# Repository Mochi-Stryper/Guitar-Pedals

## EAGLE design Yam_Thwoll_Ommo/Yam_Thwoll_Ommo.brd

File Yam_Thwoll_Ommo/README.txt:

Zvex
Woolly Mammoth
Wool (Fuzz/Gain) - B2k
Pinch (Gate) - B500k
EQ - B10k
Volume - B10k

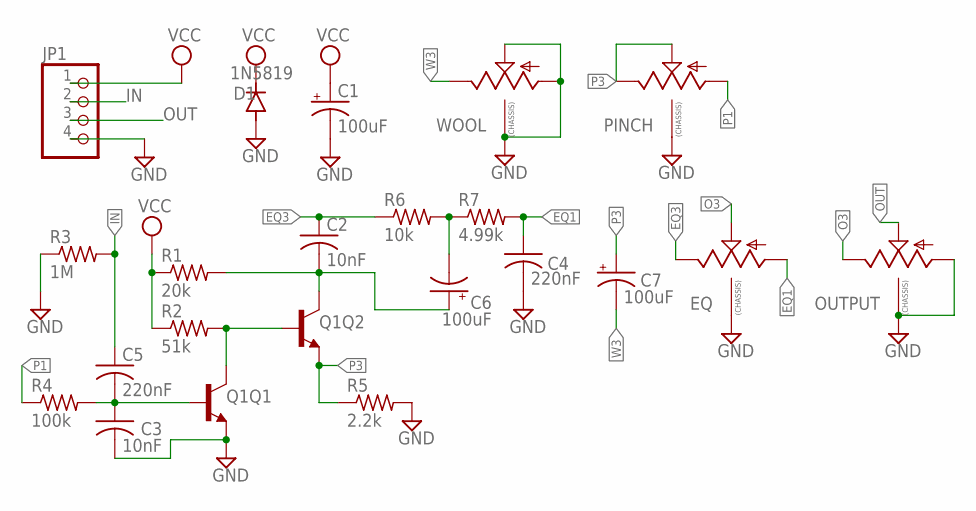
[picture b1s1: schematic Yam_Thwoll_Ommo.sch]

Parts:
C1, C6, C7: 100uF; PAN_B_SMD+THRU
C2, C3: 10nF; C0402
C4, C5: 220nF; C0402
D1: 1N5819; SOD123
EQ: 9MM_SNAP-IN_POT_CHASSIS; 9MM_SNAP-IN_POT
JP1: PINHD-1X4; 1X04
OUTPUT: 9MM_SNAP-IN_POT_CHASSIS; 9MM_SNAP-IN_POT
PINCH: 9MM_SNAP-IN_POT_CHASSIS; 9MM_SNAP-IN_POT
Q1: TRANS_NPN_DUAL-MBT3904DW1T1; SC70-6
R1: 20k; R0402
R2: 51k; R0402
R3: 1M; R0402
R4: 100k; R0402
R5: 2.2k; R0402
R6: 10k; R0402
R7: 4.99k; R0402
WOOL: 9MM_SNAP-IN_POT_CHASSIS; 9MM_SNAP-IN_POT

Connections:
EQ1: C4.1, EQ.1 (A), R7.2
EQ3: C2.1, EQ.3 (E), R6.1
GND: C1.-, C1.-- (-), C3.2, C4.2, D1.A, EQ.CHASSIS1, EQ.CHASSIS2, JP1.4, OUTPUT.1 (A), OUTPUT.CHASSIS1, OUTPUT.CHASSIS2, PINCH.CHASSIS1, PINCH.CHASSIS2, Q1.4 (E), R3.1, R5.2, WOOL.1 (A), WOOL.2 (S), WOOL.CHASSIS1, WOOL.CHASSIS2
IN: C5.1, JP1.2, R3.2
unnamed: Q1.2 (B), Q1.3 (C), R2.2
unnamed: C2.2, C6.+, C6.++ (+), Q1.6 (C), R1.2
unnamed: C6.-, C6.-- (-), R6.2, R7.1
unnamed: C3.1, C5.2, Q1.5 (B), R4.2
O3: EQ.2 (S), OUTPUT.3 (E)
OUT: JP1.3, OUTPUT.2 (S)
P1: PINCH.1 (A), R4.1
P3: C7.+, C7.++ (+), PINCH.2 (S), PINCH.3 (E), Q1.1 (E), R5.1
VCC: C1.+, C1.++ (+), D1.C, JP1.1, R1.1, R2.1
W3: C7.-, C7.-- (-), WOOL.3 (E)

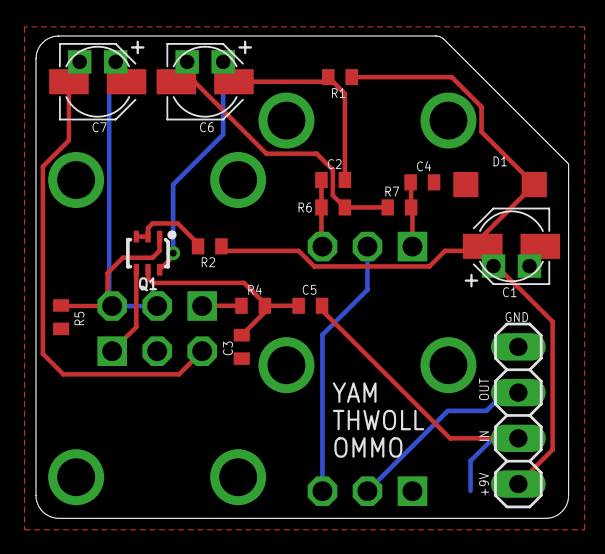
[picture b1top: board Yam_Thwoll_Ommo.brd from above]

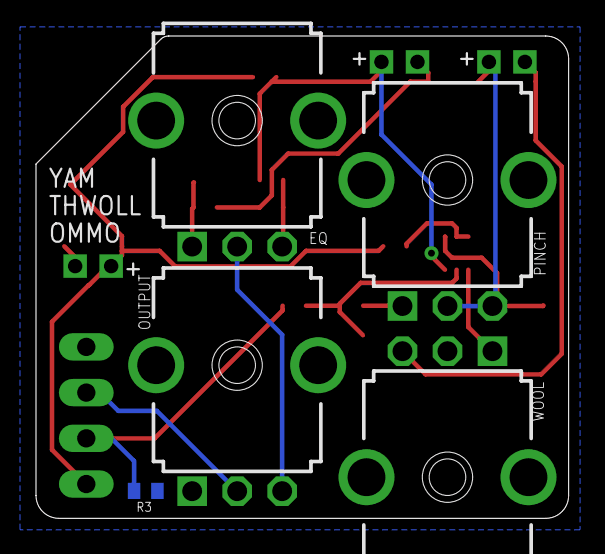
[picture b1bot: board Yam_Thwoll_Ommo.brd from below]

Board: 2 copper layers, 29.6 x 26.8 mm, 21 parts (5 on the bottom side), 14 nets.

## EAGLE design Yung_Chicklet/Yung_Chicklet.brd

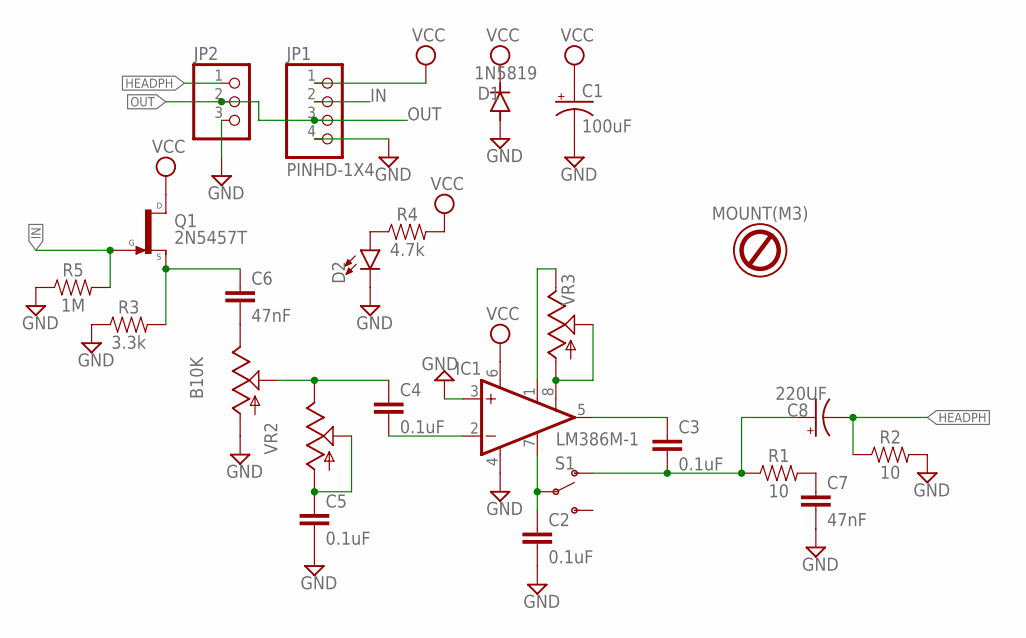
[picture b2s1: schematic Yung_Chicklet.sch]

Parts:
B10K: 9MM_SNAP-IN_POT_; 9MM_SNAP-IN_POT
C1: 100uF; PAN_B_SMD+THRU
C2, C3, C4, C5: 0.1uF; 0603
C6, C7: 47nF; 0603
C8: 220UF; PAN_B_SMD+THRU
D1: 1N5819; SOD123
D2: LED1206; LED-1206
IC1: LM386M-1; SO08
JP1: PINHD-1X4; 1X04
JP2: PINHD-1X3; 1X03
O2: MOUNT(M3); HOLE-3.5MM
Q1: 2N5457T; TO92F
R1, R2: 10; 0603
R3: 3.3k; 0603
R4: 4.7k; 0603
R5: 1M; 0603
S1: SWITCH-SPDT-PTH-11.6X4.0MM-LOCK; SWITCH_SPDT_PTH_11.6X4.0MM_LOCK
VR2, VR3: 9MM_SNAP-IN_POT_; 9MM_SNAP-IN_POT

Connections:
GND: B10K.1 (A), C1.-, C1.-- (-), C2.2, C5.2, C7.2, D1.A, D2.C, IC1.3 (+IN), IC1.4 (GND), JP1.4, JP2.3, R2.2, R3.1, R5.1
HEADPH: C8.-, C8.-- (-), JP2.1, R2.1
IN: JP1.2, Q1.1 (G), R5.2
unnamed: D2.A, R4.1
unnamed: C6.1, Q1.2 (S), R3.2
unnamed: B10K.3 (E), C6.2
unnamed: B10K.2 (S), C4.1, VR2.3 (E)
unnamed: C5.1, VR2.1 (A), VR2.2 (S)
unnamed: C4.2, IC1.2 (-IN)
unnamed: IC1.8 (GAIN), VR3.1 (A), VR3.2 (S)
unnamed: IC1.1 (GAIN), VR3.3 (E)
unnamed: C3.1, IC1.5 (OUT)
unnamed: C2.1, IC1.7 (BYPASS), S1.2
unnamed: C3.2, C8.+, C8.++ (+), R1.1, S1.1 (O)
unnamed: C7.1, R1.2
OUT: JP1.3, JP2.2
VCC: C1.+, C1.++ (+), D1.C, IC1.6 (VS), JP1.1, Q1.3 (D), R4.2

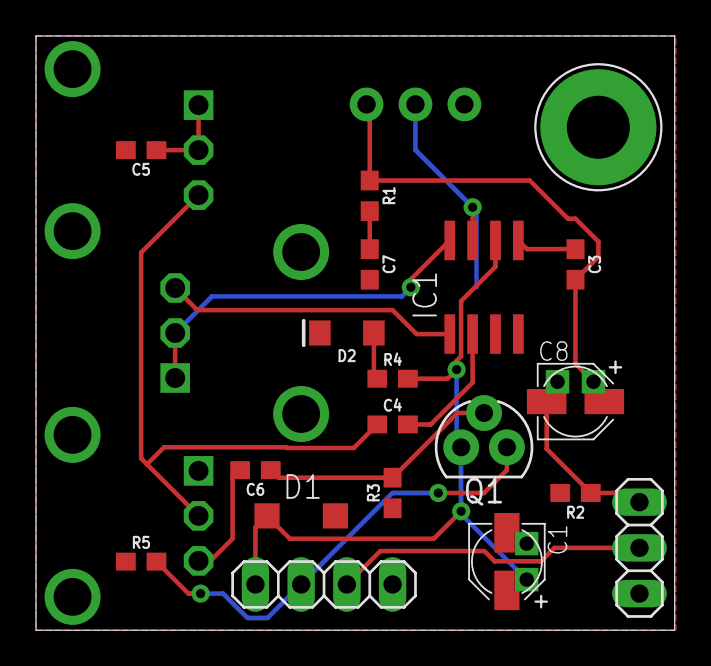
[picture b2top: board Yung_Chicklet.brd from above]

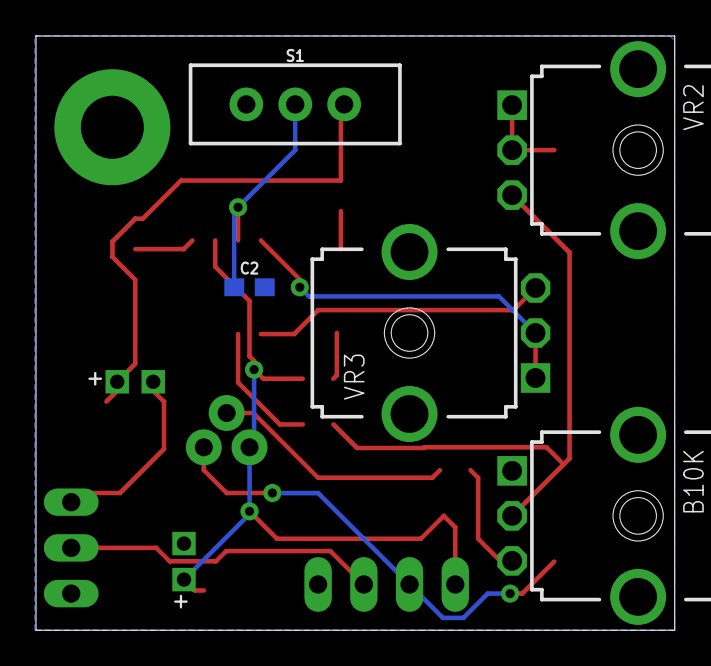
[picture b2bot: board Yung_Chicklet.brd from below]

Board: 2 copper layers, 35.5 x 33.0 mm, 24 parts (5 on the bottom side), 17 nets.

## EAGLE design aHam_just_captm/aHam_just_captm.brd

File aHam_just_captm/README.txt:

Campus
THAT Jam
Airwire:
+12V to Threshold_1
-12V to Threshold_3
-12V to Gain_1
-Ratio_3 to Knee_Switch_B1

Notes:
-Pin 20 of THAT4301 may be jumpered to N$9 and R39 omitted if no gain compensation is required.
-Busy LED may be omitted
-LT1054 daughterboard may be utilized to generate a +/-12V supply.

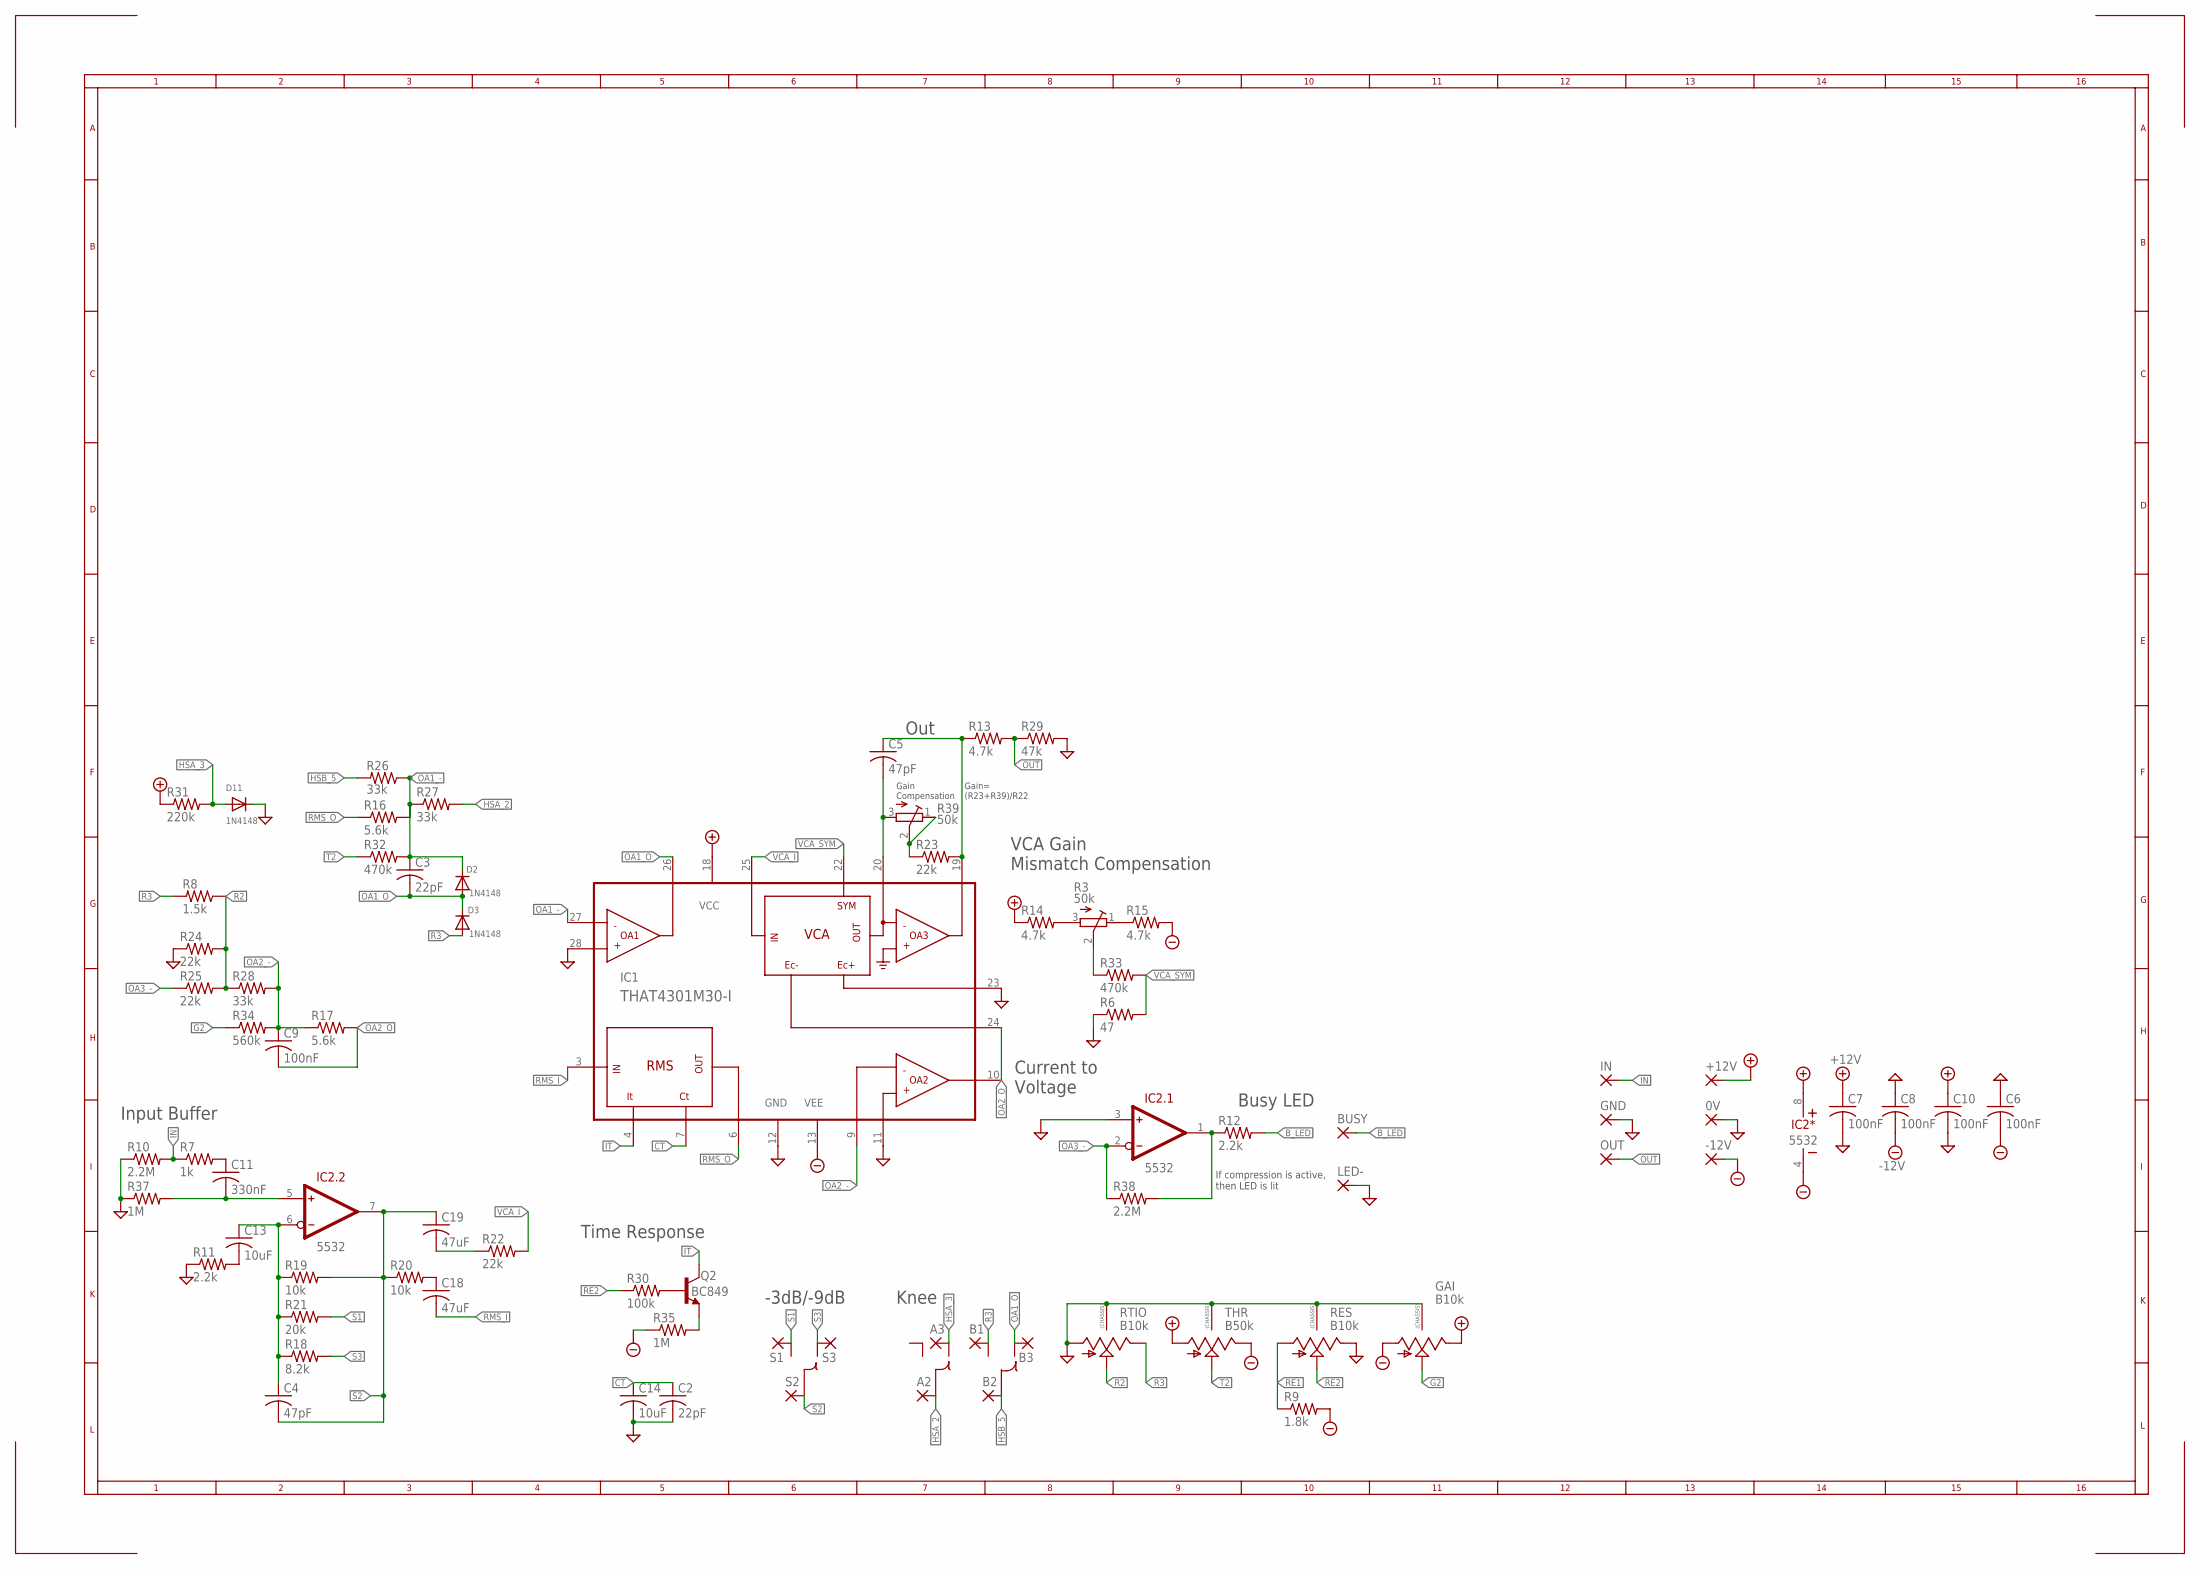
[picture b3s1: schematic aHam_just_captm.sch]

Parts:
0V: 1,6/0,8
+12V: 1,6/0,8
-12V: 1,6/0,8
A2, A3: 1,6/0,8
B1, B2, B3: 1,6/0,8
BUSY: 1,6/0,8
C2, C3: 22pF; C0805
C4, C5: 47pF; C0805
C6, C7, C8, C9, C10: 100nF; C0805
C11: 330nF; C0805
C13, C14: 10uF; C1206
C18, C19: 47uF; C1206
D2, D3, D11: 1N4148; SOD-123
GAI: B10k; 9MM_SNAP-IN_POT
GND: 1,6/0,8
IC1: THAT4301M30-I; SO30W
IC2: 5532; SO-8
IN: 1,6/0,8
LED-: 1,6/0,8
OUT: 1,6/0,8
Q2: BC849; SOT23-BEC
R3, R39: 50k; RTRIM3314G
R6: 47; R0805
R7: 1k; R0805
R8: 1.5k; R0805
R9: 1.8k; R0805
R10, R38: 2.2M; R0805
R11, R12: 2.2k; R0805
R13, R14, R15: 4.7k; R0805
R16, R17: 5.6k; R0805
R18: 8.2k; R0805
R19, R20: 10k; R0805
R21: 20k; R0805
R22, R23, R24, R25: 22k; R0805
R26, R27, R28: 33k; R0805
R29: 47k; R0805
R30: 100k; R0805
R31: 220k; R0805
R32, R33: 470k; R0805
R34: 560k; R0805
R35, R37: 1M; R0805
RES: B10k; 9MM_SNAP-IN_POT
RTIO: B10k; 9MM_SNAP-IN_POT
S1, S2, S3: 1,6/0,8
THR: B50k; 9MM_SNAP-IN_POT

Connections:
+12V: +12V.1, C7.1, C10.1, GAI.3 (E), IC1.18 (VCC), IC2.8 (V+), R14.1, R31.1, THR.1 (A)
-12V: -12V.1, C6.2, C8.2, GAI.1 (A), IC1.13 (VEE), IC2.4 (V-), R9.2, R15.2, R35.1, THR.3 (E)
B_LED: BUSY.1, R12.2
CT: C2.1, C14.1, IC1.7 (CT)
G2: GAI.2 (S), R34.1
GND: 0V.1, C2.2, C6.1, C7.2, C8.1, C10.2, C14.2, D11.C, GAI.CHASSIS1, GAI.CHASSIS2, GND.1, IC1.11 (OA2_+IN), IC1.12 (GND), IC1.23 (EC+), IC1.28 (OA1_+IN), IC2.3 (IN+), LED-.1, R6.1, R10.1, R11.1, R24.1, R29.2, R37.1, RES.3 (E), RES.CHASSIS1, RES.CHASSIS2, RTIO.1 (A), RTIO.CHASSIS1, RTIO.CHASSIS2, THR.CHASSIS1, THR.CHASSIS2
HSA_2: A2.1, R27.2
HSA_3: A3.1, D11.A, R31.2
HSB_5: B2.1, R26.2
IN: IN.1, R7.1, R10.2
IT: IC1.4 (IT), Q2.C
unnamed: C4.1, C13.1, IC2.6 (IN-), R18.1, R19.1, R21.1
unnamed: C11.1, R7.2
unnamed: C11.2, IC2.5 (IN+), R37.2
unnamed: C19.2, R22.1
unnamed: C13.2, R11.2
unnamed: C18.1, R20.2
unnamed: C5.2, IC1.20 (VCA_OUT), R39.3 (A)
unnamed: C5.1, IC1.19 (OA3_OUT), R13.1, R23.2
unnamed: R23.1, R39.1 (E), R39.2 (S)
unnamed: Q2.B, R30.2
unnamed: Q2.E, R35.2
unnamed: R3.3 (A), R14.2
unnamed: R3.1 (E), R15.1
unnamed: R3.2 (S), R33.1
unnamed: IC2.1 (OUT), R12.1, R38.2
OA1_-: C3.1, D2.C, IC1.27 (OA1_-IN), R16.2, R26.1, R27.1, R32.2
OA1_O: B3.1, C3.2, D2.A, D3.C, IC1.26 (OA1_OUT)
OA2_-: C9.1, IC1.9 (OA2_-IN), R17.1, R28.2, R34.2
OA2_O: C9.2, IC1.10 (OA2_OUT), IC1.24 (EC-), R17.2
OA3_-: IC2.2 (IN-), R25.1, R38.1
OUT: OUT.1, R13.2, R29.1
R2: R8.1, R24.2, R25.2, R28.1, RTIO.2 (S)
R3: B1.1, D3.A, R8.2, RTIO.3 (E)
RE1: R9.1, RES.1 (A)
RE2: R30.1, RES.2 (S)
RMS_I: C18.2, IC1.3 (RMS_IN)
RMS_O: IC1.6 (RMS_OUT), R16.1
S1: R21.2, S1.1
S2: C4.2, C19.1, IC2.7 (OUT), R19.2, R20.1, S2.1
S3: R18.2, S3.1
T2: R32.1, THR.2 (S)
VCA_I: IC1.25 (VCA_IN), R22.2
VCA_SYM: IC1.22 (SYM), R6.2, R33.2

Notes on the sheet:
Gain Compensation
Gain= (R23+R39)/R22
Input Buffer
Time Response
Busy LED
If compression is active, then LED is lit
Knee
-3dB/-9dB
VCA Gain Mismatch Compensation
Out
Current to Voltage

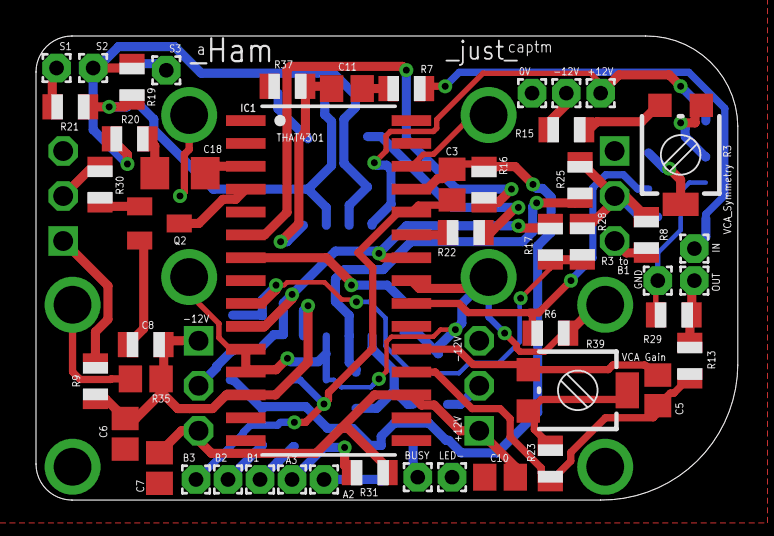
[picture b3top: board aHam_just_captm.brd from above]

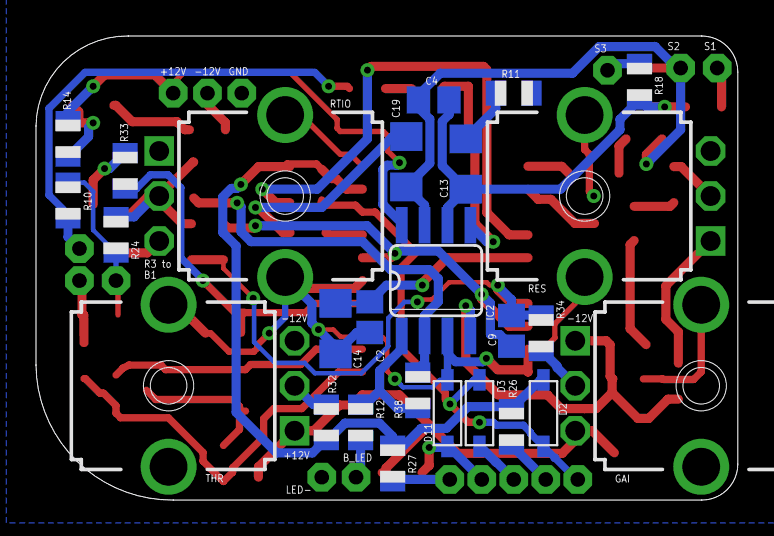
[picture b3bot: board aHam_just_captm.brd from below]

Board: 2 copper layers, 39.0 x 25.8 mm, 74 parts (26 on the bottom side), 44 nets.

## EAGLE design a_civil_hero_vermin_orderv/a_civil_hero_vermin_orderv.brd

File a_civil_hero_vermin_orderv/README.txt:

Death By Audio Inspired
Lubdar @ Madbean
Evil Harmonic Transformer
Skipped the 100nF decoupling cap and reduced the 220uF cap to 100uF.

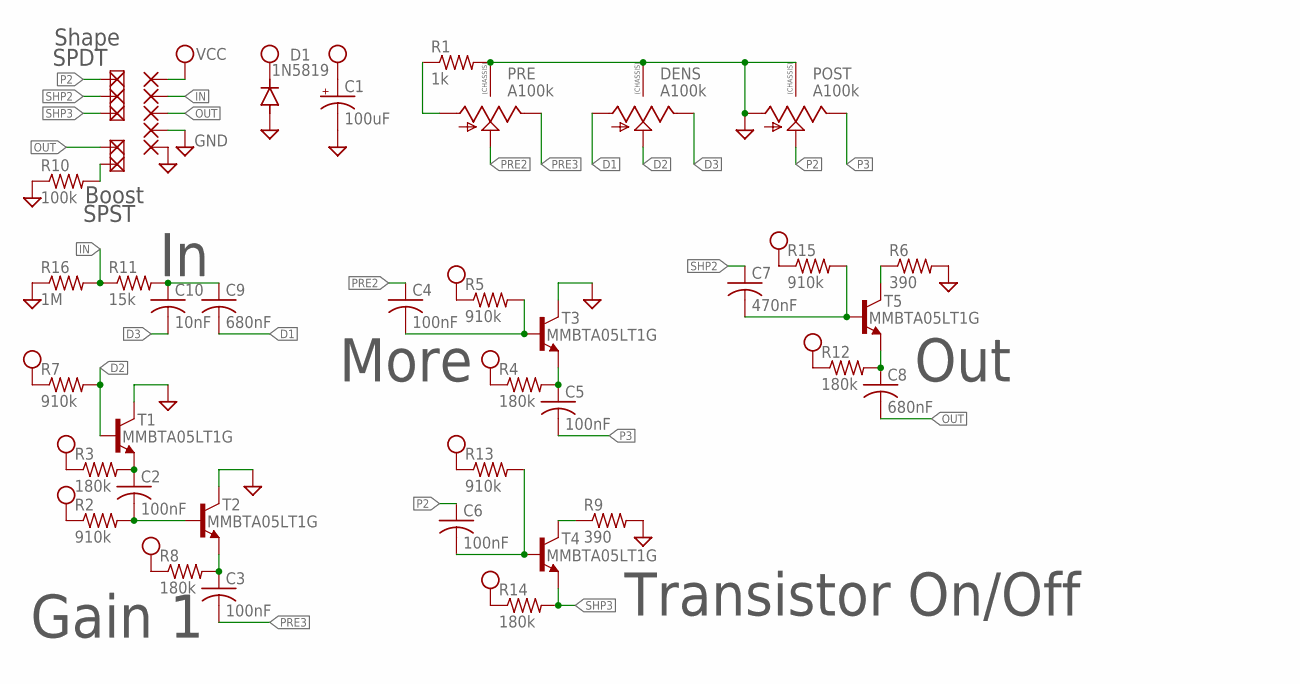
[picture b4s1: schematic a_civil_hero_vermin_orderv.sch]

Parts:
BOOST: 1,6/0,8
C1: 100uF; CPOL-RADIAL-2.5MM-6.5MM
C2, C3, C4, C5, C6: 100nF; C0603
C7: 470nF; C0603
C8, C9: 680nF; C0603
C10: 10nF; C0603
D1: 1N5819; SOD123
DENS: A100k; 9MM_SNAP-IN_POT
PAD1, PAD2, PAD3, PAD4, PAD5, PAD7: 1,6/0,8
POST: A100k; 9MM_SNAP-IN_POT
PRE: A100k; 9MM_SNAP-IN_POT
R1: 1k; R0603
R2, R5, R7, R13, R15: 910k; R0603
R3, R4, R8, R12, R14: 180k; R0603
R6, R9: 390; R0603
R10: 100k; R0603
R11: 15k; R0603
R16: 1M; R0603
SHAPE1, SHAPE2, SHAPE3: 1,6/0,8
T1, T2, T3, T4, T5: MMBTA05LT1G; SOT23-BEC

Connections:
BOOST1: BOOST.1, R10.2
D1: C9.2, DENS.1 (A)
D2: DENS.2 (S), R7.2, T1.B
D3: C10.2, DENS.3 (E)
GND: C1.2 (-), D1.A, DENS.CHASSIS1, DENS.CHASSIS2, PAD4.1, PAD7.1, POST.1 (A), POST.CHASSIS1, POST.CHASSIS2, PRE.CHASSIS1, PRE.CHASSIS2, R1.2, R6.2, R9.2, R10.1, R16.1, T1.C, T2.C, T3.C
IN: PAD2.1, R11.1, R16.2
unnamed: C3.1, R8.2, T2.E
unnamed: PRE.1 (A), R1.1
unnamed: C9.1, C10.1, R11.2
unnamed: C2.1, R3.2, T1.E
unnamed: C2.2, R2.2, T2.B
unnamed: C4.2, R5.2, T3.B
unnamed: C5.1, R4.2, T3.E
unnamed: R9.1, T4.C
unnamed: C6.2, R13.2, T4.B
unnamed: C7.2, R15.2, T5.B
unnamed: R6.1, T5.C
unnamed: C8.1, R12.2, T5.E
OUT: C8.2, PAD3.1, PAD5.1
P2: C6.1, POST.2 (S), SHAPE1.1
P3: C5.2, POST.3 (E)
PRE2: C4.1, PRE.2 (S)
PRE3: C3.2, PRE.3 (E)
SHP2: C7.1, SHAPE2.1
SHP3: R14.2, SHAPE3.1, T4.E
VCC: C1.1 (+), D1.C, PAD1.1, R2.1, R3.1, R4.1, R5.1, R7.1, R8.1, R12.1, R13.1, R14.1, R15.1

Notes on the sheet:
Gain 1
Out
More
Transistor On/Off
Boost
SPST
Shape
SPDT

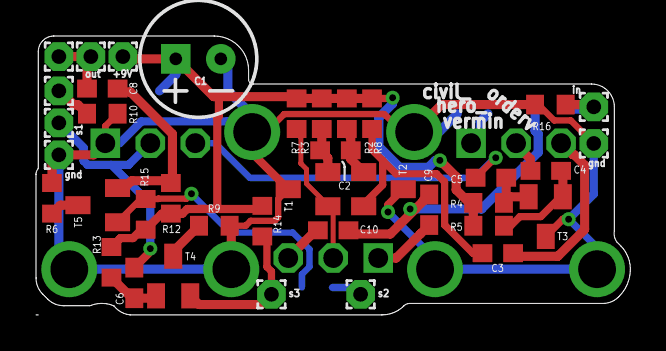
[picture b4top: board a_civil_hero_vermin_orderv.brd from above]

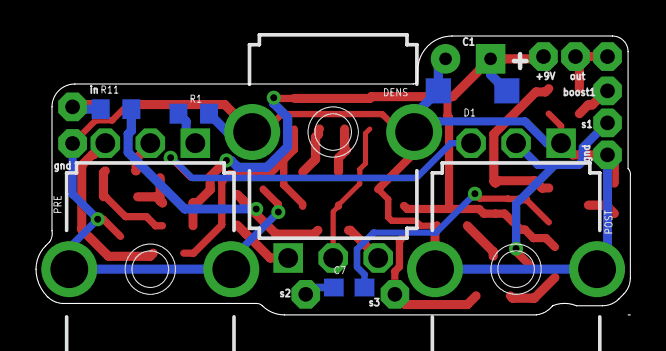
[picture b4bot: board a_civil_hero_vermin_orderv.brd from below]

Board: 2 copper layers, 33.0 x 15.5 mm, 45 parts (7 on the bottom side), 26 nets.

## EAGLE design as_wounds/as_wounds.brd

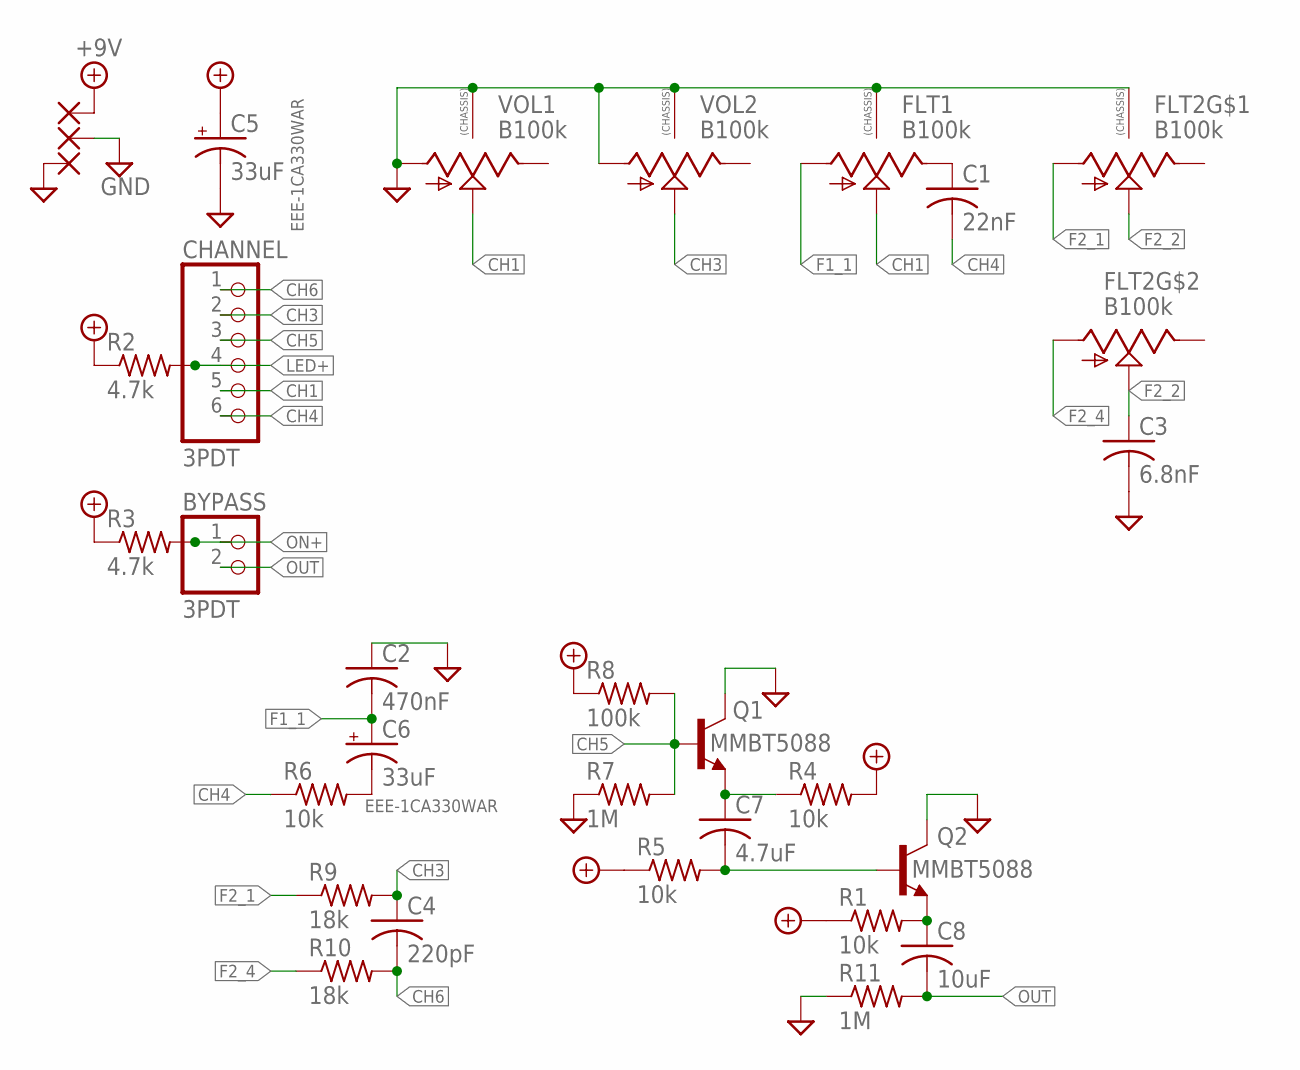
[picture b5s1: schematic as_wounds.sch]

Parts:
BYPASS: 3PDT; 1X02
C1: 22nF; C0603
C2: 470nF; C0603
C3: 6.8nF; C0603
C4: 220pF; C0603
C5, C6: 33uF; PANASONIC_C
C7: 4.7uF; C1206
C8: 10uF; C1206
CHANNEL: 3PDT; 1X06
FLT1: B100k; 9MM_SNAP-IN_POT
FLT2: B100k; DUAL_9MM_SNAP-IN_POT
PAD1, PAD2, PAD3: 1,6/0,8
Q1, Q2: MMBT5088; SOT23-BEC
R1, R4, R5, R6: 10k; R0603
R2, R3: 4.7k; R0603
R7, R11: 1M; R0603
R8: 100k; R0603
R9, R10: 18k; R0603
VOL1, VOL2: B100k; 9MM_SNAP-IN_POT

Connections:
+9V: C5.+, PAD1.1, R1.1, R2.1, R3.1, R4.2, R5.1, R8.1
CH1: CHANNEL.5, FLT1.2 (S), VOL1.2 (S)
CH3: C4.1, CHANNEL.2, R9.2, VOL2.2 (S)
CH4: C1.2, CHANNEL.6, R6.1
CH5: CHANNEL.3, Q1.B, R7.2, R8.2
CH6: C4.2, CHANNEL.1, R10.2
F1_1: C2.2, C6.+, FLT1.1 (A)
F2_1: FLT2.1 (A), R9.1
F2_2: C3.1, FLT2.2 (S), FLT2.2B (S)
F2_4: FLT2.1B (A), R10.1
GND: C2.1, C3.2, C5.-, FLT1.CHASSIS1, FLT1.CHASSIS2, FLT2.CHASSIS1, FLT2.CHASSIS2, PAD2.1, PAD3.1, Q1.C, Q2.C, R7.1, R11.1, VOL1.1 (A), VOL1.CHASSIS1, VOL1.CHASSIS2, VOL2.1 (A), VOL2.CHASSIS1, VOL2.CHASSIS2
LED+: CHANNEL.4, R2.2
unnamed: C6.-, R6.2
unnamed: C1.1, FLT1.3 (E)
unnamed: C7.1, Q1.E, R4.1
unnamed: C7.2, Q2.B, R5.2
unnamed: C8.1, Q2.E, R1.2
ON+: BYPASS.1, R3.2
OUT: BYPASS.2, C8.2, R11.2

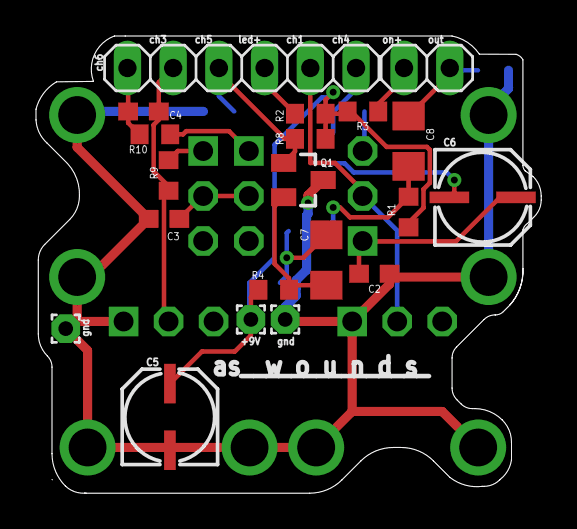
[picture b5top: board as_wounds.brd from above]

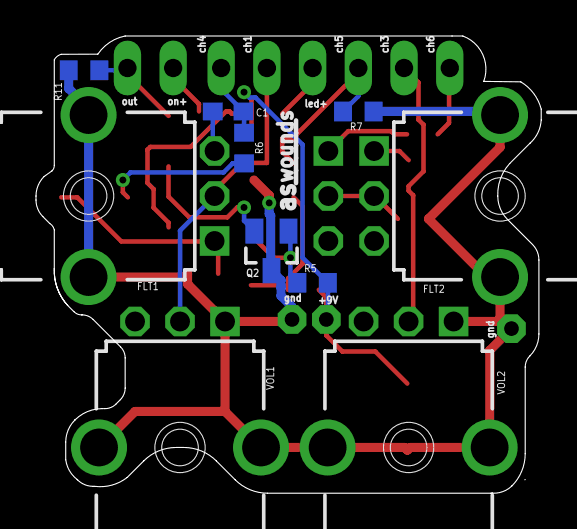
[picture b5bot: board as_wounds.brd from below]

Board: 2 copper layers, 28.1 x 25.4 mm, 30 parts (10 on the bottom side), 19 nets.

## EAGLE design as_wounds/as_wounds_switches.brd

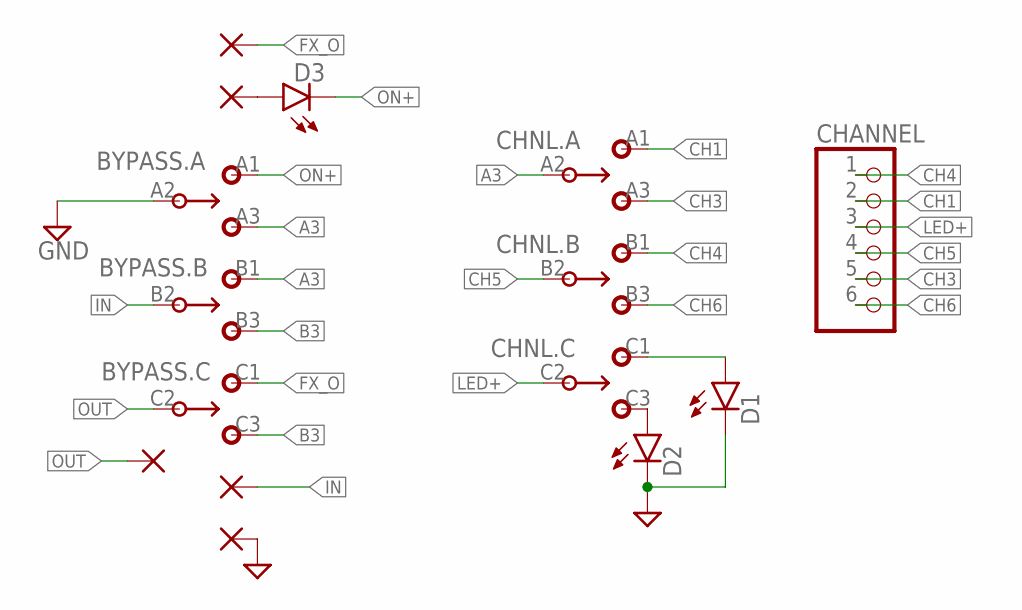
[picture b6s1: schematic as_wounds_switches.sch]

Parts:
BYPASS: 3PDT.LUGS
CHANNEL: PINHD-1X6; 1X06
CHNL: 3PDT.LUGS
D1, D2, D3: LED.1; 3MM_IO
PAD1, PAD2, PAD3, PAD4, PAD5: 1,6/0,8

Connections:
A3: BYPASS.A3 (3), BYPASS.B1 (1), CHNL.A2 (2)
B3: BYPASS.B3 (3), BYPASS.C3 (3)
CH1: CHANNEL.2, CHNL.A1 (1)
CH3: CHANNEL.5, CHNL.A3 (3)
CH4: CHANNEL.1, CHNL.B1 (1)
CH5: CHANNEL.4, CHNL.B2 (2)
CH6: CHANNEL.6, CHNL.B3 (3)
FX_O: BYPASS.C1 (1), PAD1.1
GND: BYPASS.A2 (2), D1.K (C), D2.K (C), PAD4.1
IN: BYPASS.B2 (2), PAD3.1
LED+: CHANNEL.3, CHNL.C2 (2)
unnamed: CHNL.C3 (3), D2.A
unnamed: CHNL.C1 (1), D1.A
unnamed: D3.A, PAD2.1
ON+: BYPASS.A1 (1), D3.K (C)
OUT: BYPASS.C2 (2), PAD5.1

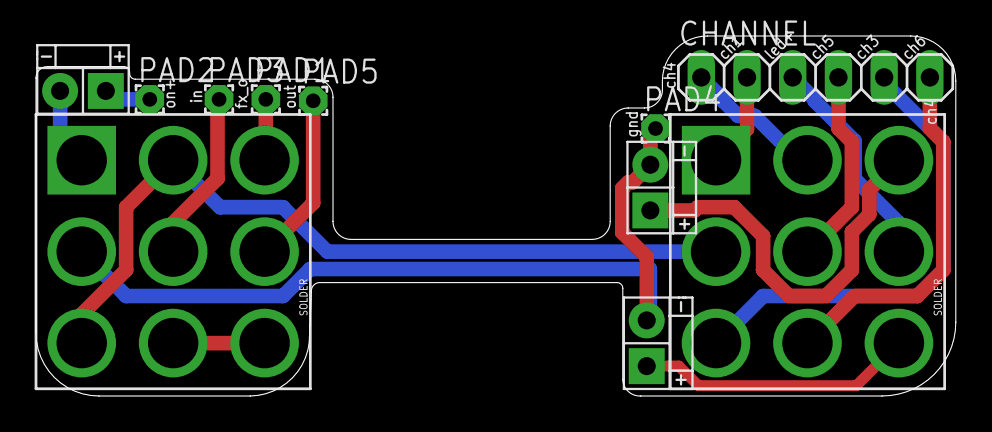
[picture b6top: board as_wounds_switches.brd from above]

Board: 2 copper layers, 51.1 x 20.0 mm, 11 parts (0 on the bottom side), 16 nets.

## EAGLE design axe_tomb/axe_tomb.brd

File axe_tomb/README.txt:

DOD
FX32 Meatbox
M51134 "secret sauce" subharmonic bass emphasizer IC

Design notes:
In the original schematic a voltage divider is creating a bias voltage of ~6VDC.
The internal 5V regulator is not being utilized to supply DVCC to the DVCC pin, which is rated to handle 4.5V-5.5V.
*edit* I've opted to connect DVCC to the internal 5V regulator. There is no external decoupling on this regulator. It may be worthwhile to implement a capacitor to ground to decouple the power on the DVCC pins
It may be worth simplifying the layout to use 5V from the M51134P regulator as a bias voltage. Alternatively, it may be more viable to craft a 1/2VCC rail from the 9V rail using a voltage divider to supply power and combine the Vbias and DVCC nets. 
It is intended that the M51134P is placed in a DIP20 socket. There should be adequate clearance on the solder side of the board for the components placed below the chip. If no socket is used, then take care that the IC is seated correctly above the components below.

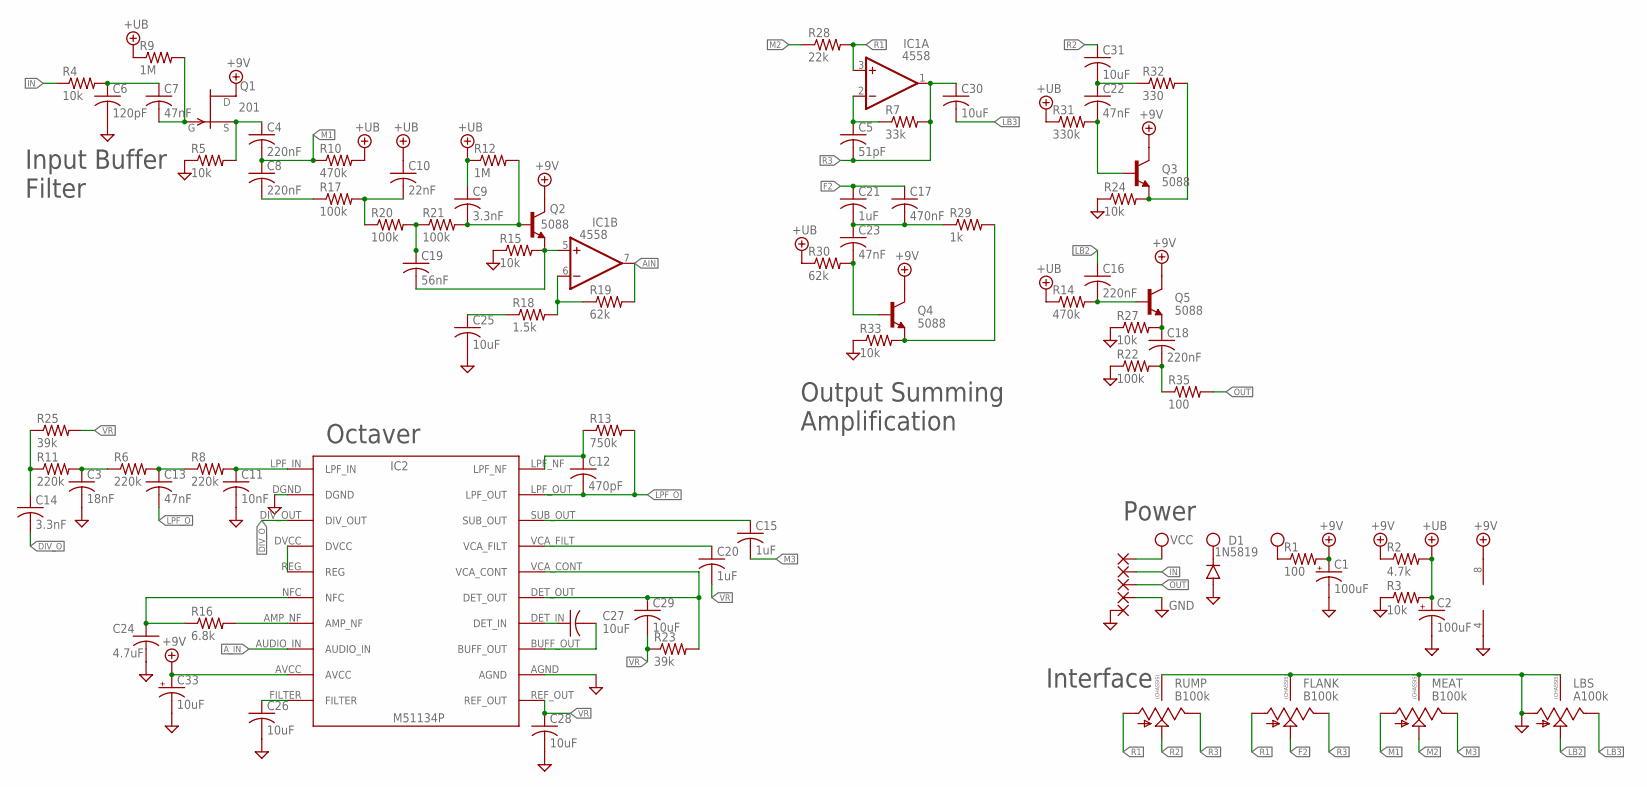
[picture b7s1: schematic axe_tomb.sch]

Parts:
C1, C2: 100uF; CPOL-RADIAL-2.5MM-6.5MM
C3: 18nF; C0603
C4, C8, C16, C18: 220nF; C0603
C5: 51pF; C0603
C6: 120pF; C0603
C7, C13, C22, C23: 47nF; C0603
C9, C14: 3.3nF; C0603
C10: 22nF; C0603
C11: 10nF; C0603
C12: 470pF; C0603
C15, C20, C21: 1uF; C0603
C17: 470nF; C0603
C19: 56nF; C0603
C24: 4.7uF; C1206
C25, C26, C27, C28, C29, C30, C31: 10uF; C1206
C33: 10uF; CAPMP3216X180N
D1: 1N5819; SOD123
FLANK: B100k; 9MM_SNAP-IN_POT
IC1: 4558; SO08
IC2: M51134P
LBS: A100k; 9MM_SNAP-IN_POT
MEAT: B100k; 9MM_SNAP-IN_POT
PAD1, PAD2, PAD3, PAD4, PAD5: 1,6/0,8
Q1: 201; SOT23
Q2, Q3, Q4, Q5: 5088; SOT23
R1: 100; R0805
R2: 4.7k; R0603
R3, R4, R5, R15, R24, R27, R33: 10k; R0603
R6, R8, R11: 220k; R0603
R7: 33k; R0603
R9, R12: 1M; R0603
R10, R14: 470k; R0603
R13: 750k; R0603
R16: 6.8k; R0603
R17, R20, R21, R22: 100k; R0603
R18: 1.5k; R0603
R19, R30: 62k; R0603
R23, R25: 39k; R0603
R28: 22k; R0603
R29: 1k; R0603
R31: 330k; R0603
R32: 330; R0603
R35: 100; R0603
RUMP: B100k; 9MM_SNAP-IN_POT

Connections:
+9V: C1.1 (+), C33.1 (+), IC1.8 (V+), IC2.AVCC, Q1.1 (D), Q2.3 (C), Q3.3 (C), Q4.3 (C), Q5.3 (C), R1.2, R2.1
+UB: C2.1 (+), C9.1, C10.1, R2.2, R3.2, R9.1, R10.2, R12.1, R14.1, R30.1, R31.1
AIN: IC1.7 (OUT), R19.2
A_IN: IC2.AUDIO_IN
DIV_O: C14.2, IC2.DIV_OUT
F2: C17.1, C21.1, FLANK.2 (S)
GND: C1.2 (-), C2.2 (-), C3.2, C6.2, C11.2, C24.2, C25.2, C26.2, C28.2, C33.2 (-), D1.A, FLANK.CHASSIS1, FLANK.CHASSIS2, IC1.4 (V-), IC2.AGND, IC2.DGND, LBS.1 (A), LBS.CHASSIS1, LBS.CHASSIS2, MEAT.CHASSIS1, MEAT.CHASSIS2, PAD4.1, PAD5.1, R3.1, R5.1, R15.1, R22.1, R24.1, R27.1, R33.1, RUMP.CHASSIS1, RUMP.CHASSIS2
IN: PAD2.1, R4.1
LB2: C16.1, LBS.2 (S)
LB3: C30.2, LBS.3 (E)
LPF_O: C12.2, C13.2, IC2.LPF_OUT, R13.2
M1: C4.2, C8.1, MEAT.1 (A), R10.1
M2: MEAT.2 (S), R28.1
M3: C15.2, MEAT.3 (E)
unnamed: C6.1, C7.1, R4.2
unnamed: C7.2, Q1.3 (G), R9.2
unnamed: C4.1, Q1.2 (S), R5.2
unnamed: C8.2, R17.1
unnamed: C10.2, R17.2, R20.1
unnamed: C19.1, R20.2, R21.1
unnamed: C9.2, Q2.1 (B), R12.2, R21.2
unnamed: C19.2, IC1.5 (+IN), Q2.2 (E), R15.2
unnamed: IC1.6 (-IN), R18.2, R19.1
unnamed: IC2.AMP_NF, R16.2
unnamed: C25.1, R18.1
unnamed: C24.1, IC2.NFC, R16.1
unnamed: IC2.DVCC, IC2.REG
unnamed: C27.1, IC2.DET_IN
unnamed: C26.1, IC2.FILTER
unnamed: C27.2, IC2.BUFF_OUT
unnamed: C29.1, IC2.DET_OUT, IC2.VCA_CONT, R23.2
unnamed: C20.1, IC2.VCA_FILT
unnamed: C11.1, IC2.LPF_IN, R8.2
unnamed: C13.1, R6.2, R8.1
unnamed: C3.1, R6.1, R11.2
unnamed: C14.1, R11.1, R25.1
unnamed: C15.1, IC2.SUB_OUT
unnamed: C12.1, IC2.LPF_NF, R13.1
unnamed: C5.1, IC1.2 (-IN), R7.1
unnamed: C22.1, C31.2, R32.1
unnamed: C22.2, Q3.1 (B), R31.2
unnamed: Q3.2 (E), R24.2, R32.2
unnamed: C17.2, C21.2, C23.1, R29.1
unnamed: C23.2, Q4.1 (B), R30.2
unnamed: Q4.2 (E), R29.2, R33.2
unnamed: C16.2, Q5.1 (B), R14.2
unnamed: C18.1, Q5.2 (E), R27.2
unnamed: C18.2, R22.2, R35.1
OUT: PAD3.1, R35.2
R1: FLANK.1 (A), IC1.3 (+IN), R28.2, RUMP.1 (A)
R2: C31.1, RUMP.2 (S)
R3: C5.2, C30.1, FLANK.3 (E), IC1.1 (OUT), R7.2, RUMP.3 (E)
VCC: D1.C, PAD1.1, R1.1
VR: C20.2, C28.1, C29.2, IC2.REF_OUT, R23.1, R25.2

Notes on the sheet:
Input Buffer Filter
Octaver
Output Summing Amplification
Power
Interface

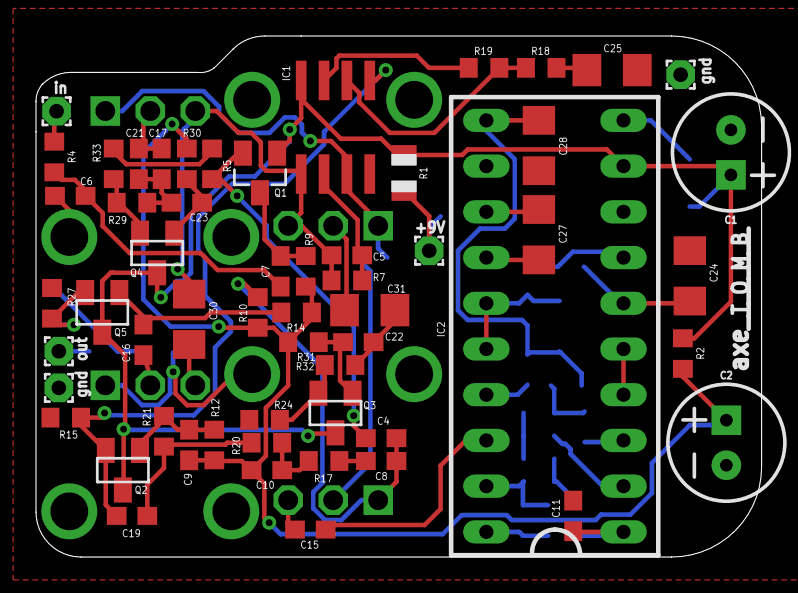
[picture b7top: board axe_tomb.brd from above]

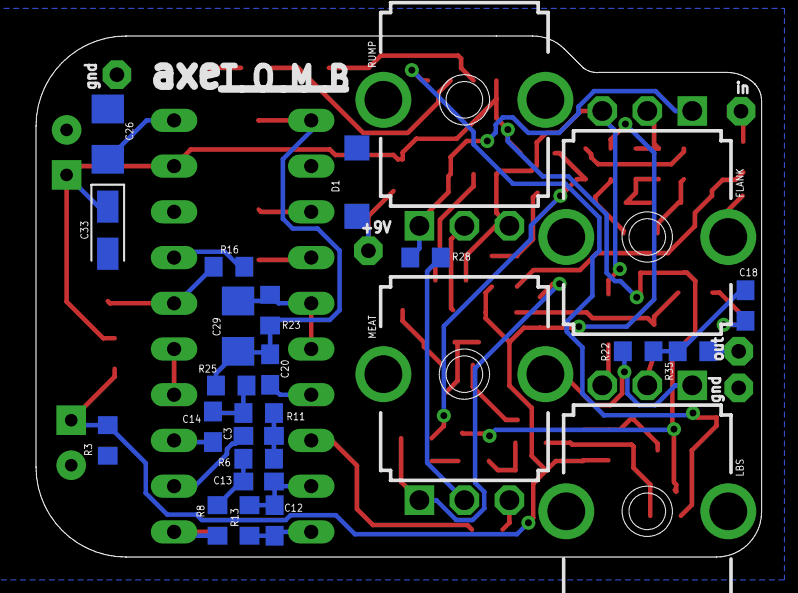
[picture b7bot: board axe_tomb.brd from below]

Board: 2 copper layers, 40.3 x 28.9 mm, 82 parts (25 on the bottom side), 53 nets.

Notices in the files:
parts and their libraries:
SparkFun-DiscreteSemi: Licensing: Creative Commons ShareAlike 4.0 International - https://creativecommons.org/licenses/by-sa/4.0
that-corp: Copyright (C) 2008-2010, Bob Starr
princeton-tech: Copyright (C) 2010, Bob Starr
